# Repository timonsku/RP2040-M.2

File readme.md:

## RP2040 M.2 USB Card

### Description
A prototype to demonstrate a M.2 card using the B-Key formfactor using the USB port present on M.2 B-Key slots.
May contain bugs so use with caution.

Twitter thread with more context: https://twitter.com/timonsku/status/1376209933381816324

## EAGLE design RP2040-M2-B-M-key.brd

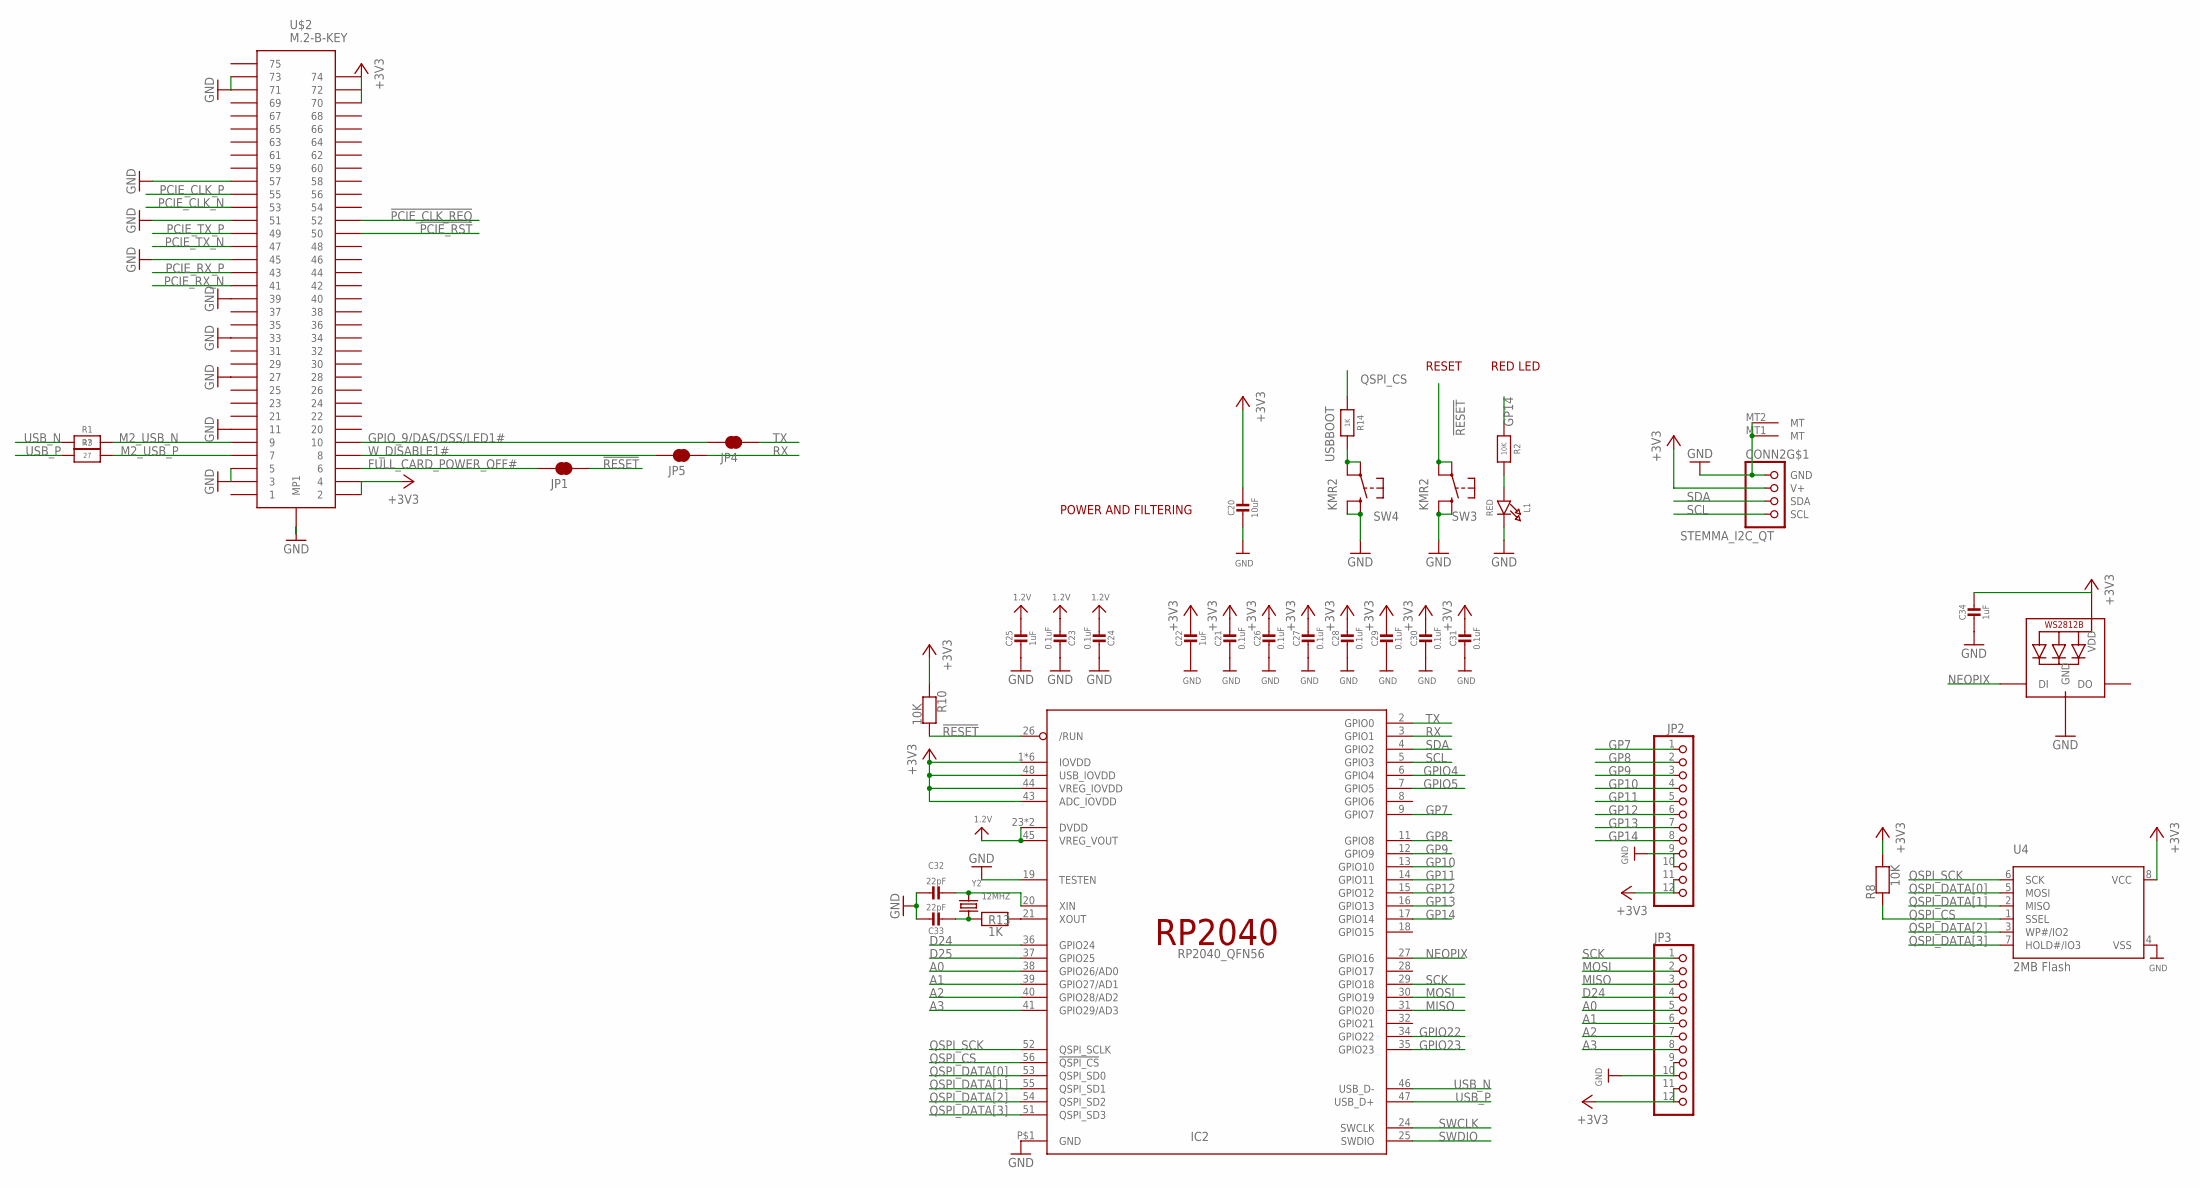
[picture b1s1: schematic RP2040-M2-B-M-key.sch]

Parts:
C20: 10uF; 0805-NO
C21, C23, C24, C26, C27, C28, C29, C30, C31: 0.1uF; _0402MP
C22, C25, C34: 1uF; _0402MP
C32, C33: 22pF; _0402MP
CONN2: STEMMA_I2C_QT; JST_SH4
IC2: RP2040_QFN56; QFN56_7MM_REDUCEDEPAD
JP1, JP4, JP5: JUMPER-SMT_2_NC_TRACE_NO-SILK; SMT-JUMPER_2_NC_TRACE_NO-SILK
JP2, JP3: HEADER-1X12; 1X12_ROUND
L1: RED; CHIPLED_0603_NOOUTLINE
LED2: WS2812B3535; LED3535
R1, R3: 27; _0402MP
R2, R8, R10: 10K; _0402MP
R13, R14: 1K; _0402MP
SW3, SW4: KMR2; BTN_KMR2_4.6X2.8
U4: 2MB Flash; SOIC8_208MIL
U$2: M.2-B-KEY
Y2: 12MHZ; CRYSTAL_3.2X2.5

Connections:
1.2V: C23.2, C24.2, C25.1, IC2.23 (DVDD), IC2.45 (VREG_VOUT), IC2.50 (DVDD)
!PCIE_CLK_REQ: U$2.P$52 (52)
!PCIE_RST: U$2.P$50 (50)
!RESET: IC2.26 (/RUN), JP1.2, R10.2, SW3.A, SW3.A' (P1)
+3V3: C20.1, C21.1, C22.1, C26.1, C27.1, C28.1, C29.1, C30.1, C31.1, C34.1, CONN2.2 (V+), IC2.1 (IOVDD), IC2.10 (IOVDD), IC2.22 (IOVDD), IC2.33 (IOVDD), IC2.42 (IOVDD), IC2.43 (ADC_IOVDD), IC2.44 (VREG_IOVDD), IC2.48 (USB_IOVDD), IC2.49 (IOVDD), JP2.11, JP2.12, JP3.11, JP3.12, LED2.2 (VDD), R8.2, R10.1, U4.8 (VCC), U$2.P$2 (2), U$2.P$4 (4), U$2.P$70 (70), U$2.P$72 (72), U$2.P$74 (74)
A0: IC2.38 (GPIO26/AD0), JP3.5
A1: IC2.39 (GPIO27/AD1), JP3.6
A2: IC2.40 (GPIO28/AD2), JP3.7
A3: IC2.41 (GPIO29/AD3), JP3.8
D24: IC2.36 (GPIO24), JP3.4
D25: IC2.37 (GPIO25)
FULL_CARD_POWER_OFF#: JP1.1, U$2.P$6 (6)
GND: C20.2, C21.2, C22.2, C23.1, C24.1, C25.2, C26.2, C27.2, C28.2, C29.2, C30.2, C31.2, C32.1, C33.1, C34.2, CONN2.1 (GND), CONN2.MT1 (MT), CONN2.MT2 (MT), IC2.19 (TESTEN), IC2.P$1 (GND), JP2.9, JP2.10, JP3.9, JP3.10, L1.C, LED2.4 (GND), SW3.B (S), SW3.B' (S1), SW4.B (S), SW4.B' (S1), U4.4 (VSS), U$2.MOUNTING-HOLE (MP1), U$2.P$3 (3), U$2.P$5 (5), U$2.P$11 (11), U$2.P$27 (27), U$2.P$33 (33), U$2.P$39 (39), U$2.P$45 (45), U$2.P$51 (51), U$2.P$57 (57), U$2.P$71 (71), U$2.P$73 (73)
GP7: IC2.9 (GPIO7), JP2.1
GP8: IC2.11 (GPIO8), JP2.2
GP9: IC2.12 (GPIO9), JP2.3
GP10: IC2.13 (GPIO10), JP2.4
GP11: IC2.14 (GPIO11), JP2.5
GP12: IC2.15 (GPIO12), JP2.6
GP13: IC2.16 (GPIO13), JP2.7
GP14: IC2.17 (GPIO14), JP2.8, R2.1
GPIO4: IC2.6 (GPIO4)
GPIO5: IC2.7 (GPIO5)
GPIO22: IC2.34 (GPIO22)
GPIO23: IC2.35 (GPIO23)
GPIO_9/DAS/DSS/LED1#: JP4.1, U$2.P$10 (10)
M2_USB_N: R1.2, U$2.P$9 (9)
M2_USB_P: R3.2, U$2.P$7 (7)
MISO: IC2.31 (GPIO20), JP3.3
MOSI: IC2.30 (GPIO19), JP3.2
unnamed: L1.A, R2.2
unnamed: IC2.21 (XOUT), R13.2
unnamed: C32.2, IC2.20 (XIN), Y2.2
unnamed: C33.2, R13.1, Y2.1
NEOPIX: IC2.27 (GPIO16), LED2.1 (DI)
PCIE_CLK_N: U$2.P$53 (53)
PCIE_CLK_P: U$2.P$55 (55)
PCIE_RX_N: U$2.P$41 (41)
PCIE_RX_P: U$2.P$43 (43)
PCIE_TX_N: U$2.P$47 (47)
PCIE_TX_P: U$2.P$49 (49)
QSPI_CS: IC2.56 (!QSPI_CS), R8.1, R14.1, U4.1 (SSEL)
QSPI_DATA[0]: IC2.53 (QSPI_SD0), U4.5 (MOSI)
QSPI_DATA[1]: IC2.55 (QSPI_SD1), U4.2 (MISO)
QSPI_DATA[2]: IC2.54 (QSPI_SD2), U4.3 (WP#/IO2)
QSPI_DATA[3]: IC2.51 (QSPI_SD3), U4.7 (HOLD#/IO3)
QSPI_SCK: IC2.52 (QSPI_SCLK), U4.6 (SCK)
RX: IC2.3 (GPIO1), JP5.2
SCK: IC2.29 (GPIO18), JP3.1
SCL: CONN2.4 (SCL), IC2.5 (GPIO3)
SDA: CONN2.3 (SDA), IC2.4 (GPIO2)
SWCLK: IC2.24 (SWCLK)
SWDIO: IC2.25 (SWDIO)
TX: IC2.2 (GPIO0), JP4.2
USBBOOT: R14.2, SW4.A, SW4.A' (P1)
USB_N: IC2.46 (USB_D-), R1.1
USB_P: IC2.47 (USB_D+), R3.1
W_DISABLE1#: JP5.1, U$2.P$8 (8)

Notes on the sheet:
POWER AND FILTERING
RESET
RED LED

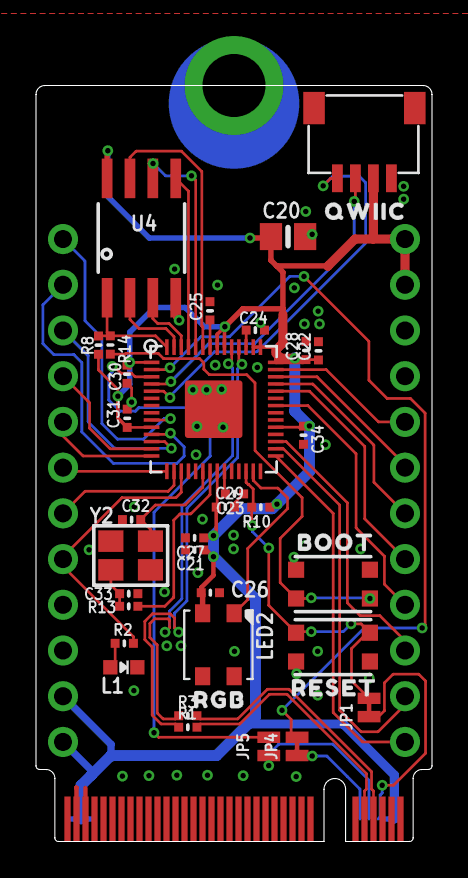
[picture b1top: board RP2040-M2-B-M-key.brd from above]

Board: 2 copper layers, 22.0 x 42.0 mm, 41 parts (1 on the bottom side), 43 nets.

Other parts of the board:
U$4: BOOT0
U$5: RESET0
U$6: QWIIC0
U$7: RGB0
U$8: DIODES-DELIGHT-LOGO-10X10-TPLACE

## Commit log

2022-10-27 add readme
2022-10-27 add license

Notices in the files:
parts and their libraries:
Custom-Parts: Copyright: Timon Skerutsch
License: CC-BY-SA
microbuilder: This work is placed in the public domain, and may be freely used for commercial and non-commercial work with the following conditions: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
